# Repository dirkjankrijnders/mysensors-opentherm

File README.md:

# mysensors-opentherm
Mysensors opentherm gateway

Effectively a open of http://otgw.tclcode.com, but with external power brick and a MYSX-2.0 connector instead of the RS-232 interface. The PCB is designed to fit in [this](http://www.ebay.com/itm/221899779029) enclosure and connect to https://github.com/dirkjankrijnders/MYS-PMS7003.

3D render of the PCB:

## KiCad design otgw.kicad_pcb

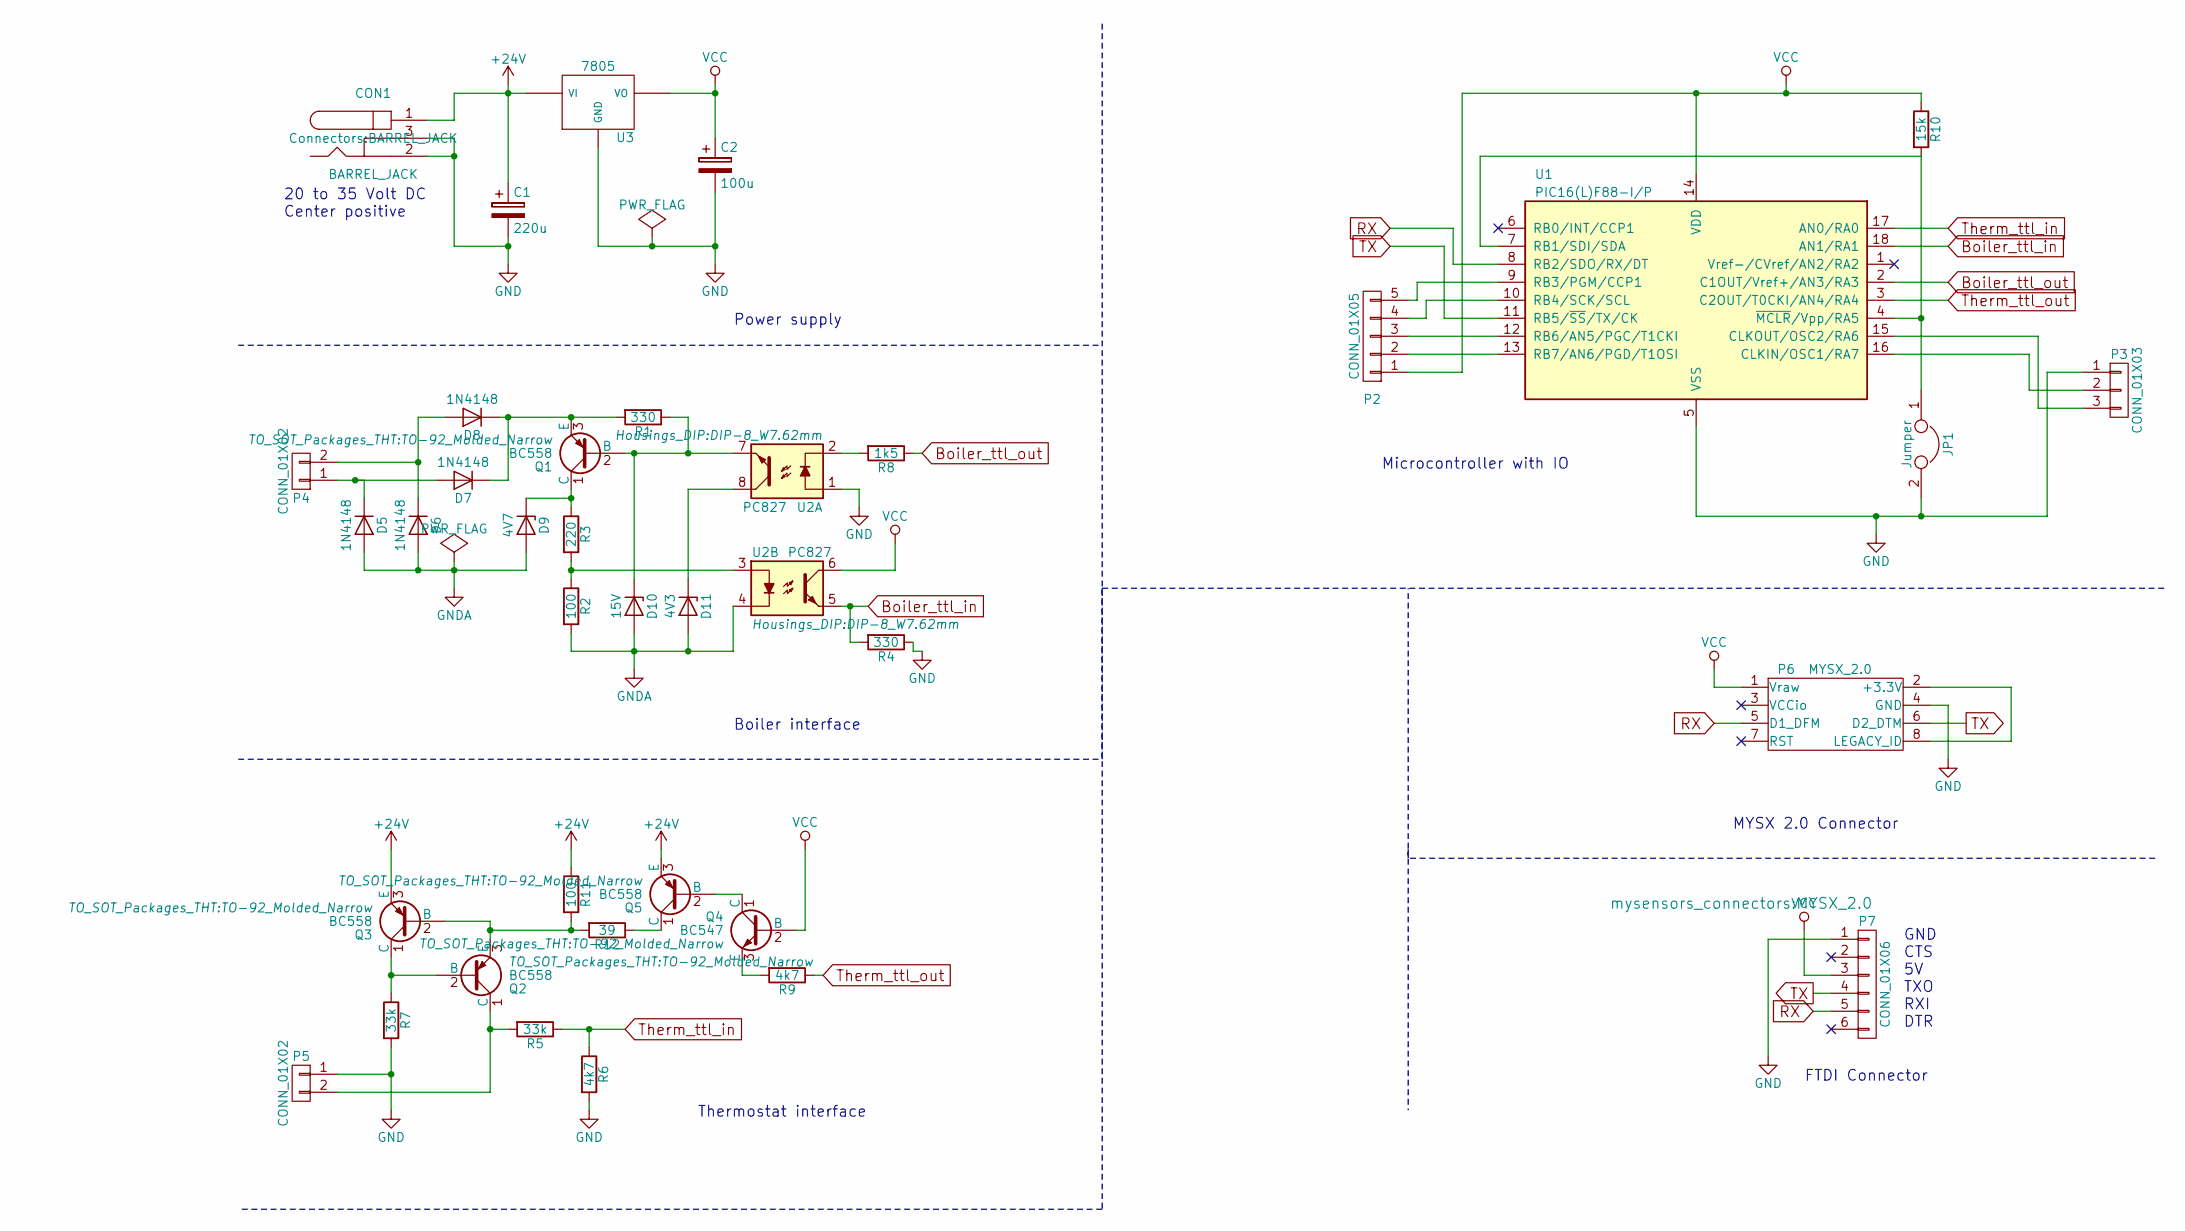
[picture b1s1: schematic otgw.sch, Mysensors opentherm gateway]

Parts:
C1: 220u; CP_Radial_D10.0mm_P5.00mm_P7.50mm
C2: 100u; CP_Radial_D10.0mm_P5.00mm_P7.50mm
CON1: BARREL_JACK
D5, D6, D7, D8: 1N4148; D_DO-35_SOD27_P7.62mm_Horizontal
D9: 4V7; D_DO-35_SOD27_P7.62mm_Horizontal
D10: 15V; D_DO-35_SOD27_P7.62mm_Horizontal
D11: 4V3; D_DO-35_SOD27_P7.62mm_Horizontal
JP1: Jumper; Pin_Header_Angled_1x02_Pitch2.54mm
P2: CONN_01X05; Pin_Header_Straight_1x05_Pitch2.54mm
P3: CONN_01X03; Pin_Header_Straight_1x03_Pitch2.54mm
P4, P5: CONN_01X02; PhoenixContact_MSTBA-G_02x5.00mm_Angled
P6: MYSX_2.0
P7: CONN_01X06; Pin_Header_Straight_1x06_Pitch2.54mm
Q1, Q2, Q3, Q5: BC558; TO-92_Molded_Narrow
Q4: BC547; TO-92_Molded_Narrow
R1, R4: 330; R_Axial_DIN0207_L6.3mm_D2.5mm_P7.62mm_Horizontal
R2, R11: 100; R_Axial_DIN0207_L6.3mm_D2.5mm_P7.62mm_Horizontal
R3: 220; R_Axial_DIN0207_L6.3mm_D2.5mm_P7.62mm_Horizontal
R5, R7: 33k; R_Axial_DIN0207_L6.3mm_D2.5mm_P7.62mm_Horizontal
R6, R9: 4k7; R_Axial_DIN0207_L6.3mm_D2.5mm_P7.62mm_Horizontal
R8: 1k5; R_Axial_DIN0207_L6.3mm_D2.5mm_P7.62mm_Horizontal
R10: 15k; R_Axial_DIN0207_L6.3mm_D2.5mm_P7.62mm_Horizontal
R12: 39; R_Axial_DIN0207_L6.3mm_D2.5mm_P7.62mm_Horizontal
U1: PIC16(L)F88-I/P; DIP-18_W7.62mm
U2: PC827; DIP-8_W7.62mm
U3: 7805; TO-220_Vertical

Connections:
+24V: C1.1, CON1.1, Q3.3 (E), Q5.3 (E), R11.1, U3.1 (VI)
Boiler_ttl_in: R4.2, U1.18 (AN1/RA1), U2.5
Boiler_ttl_out: R8.1, U1.2 (C1OUT/Vref+/AN3/RA3)
GND: C1.2, C2.2, CON1.2, CON1.3, JP1.2, P3.1, P5.1, P6.4 (GND), P7.1, R4.1, R6.2, R7.2, U1.5 (VSS), U2.1, U3.2 (GND)
GNDA: D5.2 (A), D6.2 (A), D9.2 (A), D10.2 (A), D11.2 (A), R2.2, U2.4
unnamed: D5.1 (K), D7.2 (A), P4.1
unnamed: D6.1 (K), D8.2 (A), P4.2
unnamed: D7.1 (K), D8.1 (K), Q1.3 (E), R1.2
unnamed: D9.1 (K), Q1.1 (C), R3.1
unnamed: D10.1 (K), Q1.2 (B), R1.1, U2.7
unnamed: D11.1 (K), U2.8
unnamed: JP1.1, R10.2, U1.4 (~MCLR~/Vpp/RA5), U1.7 (RB1/SDI/SDA)
unnamed: P2.2, U1.13 (RB7/AN6/PGD/T1OSI)
unnamed: P2.3, U1.12 (RB6/AN5/PGC/T1CKI)
unnamed: P2.4, U1.10 (RB4/SCK/SCL)
unnamed: P2.5, U1.9 (RB3/PGM/CCP1)
unnamed: P3.2, U1.16 (CLKIN/OSC1/RA7)
unnamed: P3.3, U1.15 (CLKOUT/OSC2/RA6)
unnamed: P5.2, Q2.1 (C), R5.2
unnamed: P6.2 (+3.3V), P6.8 (LEGACY_ID)
unnamed: Q2.2 (B), Q3.1 (C), R7.1
unnamed: Q2.3 (E), Q3.2 (B), R11.2, R12.2
unnamed: Q4.1 (C), Q5.2 (B)
unnamed: Q4.3 (E), R9.2
unnamed: Q5.1 (C), R12.1
unnamed: R2.1, R3.2, U2.3
unnamed: R8.2, U2.2
RX: P6.5 (D1_DFM), P7.5, U1.8 (RB2/SDO/RX/DT)
TX: P6.6 (D2_DTM), P7.4, U1.11 (RB5/~SS~/TX/CK)
Therm_ttl_in: R5.1, R6.1, U1.17 (AN0/RA0)
Therm_ttl_out: R9.1, U1.3 (C2OUT/T0CKI/AN4/RA4)
VCC: C2.1, P2.1, P6.1 (Vraw), P7.3, Q4.2 (B), R10.1, U1.14 (VDD), U2.6, U3.3 (VO)

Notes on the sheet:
GND CTS 5V TXO RXI DTR
MYSX 2.0 Connector
FTDI Connector
Thermostat interface
Boiler interface
Power supply
20 to 35 Volt DC Center positive
Microcontroller with IO

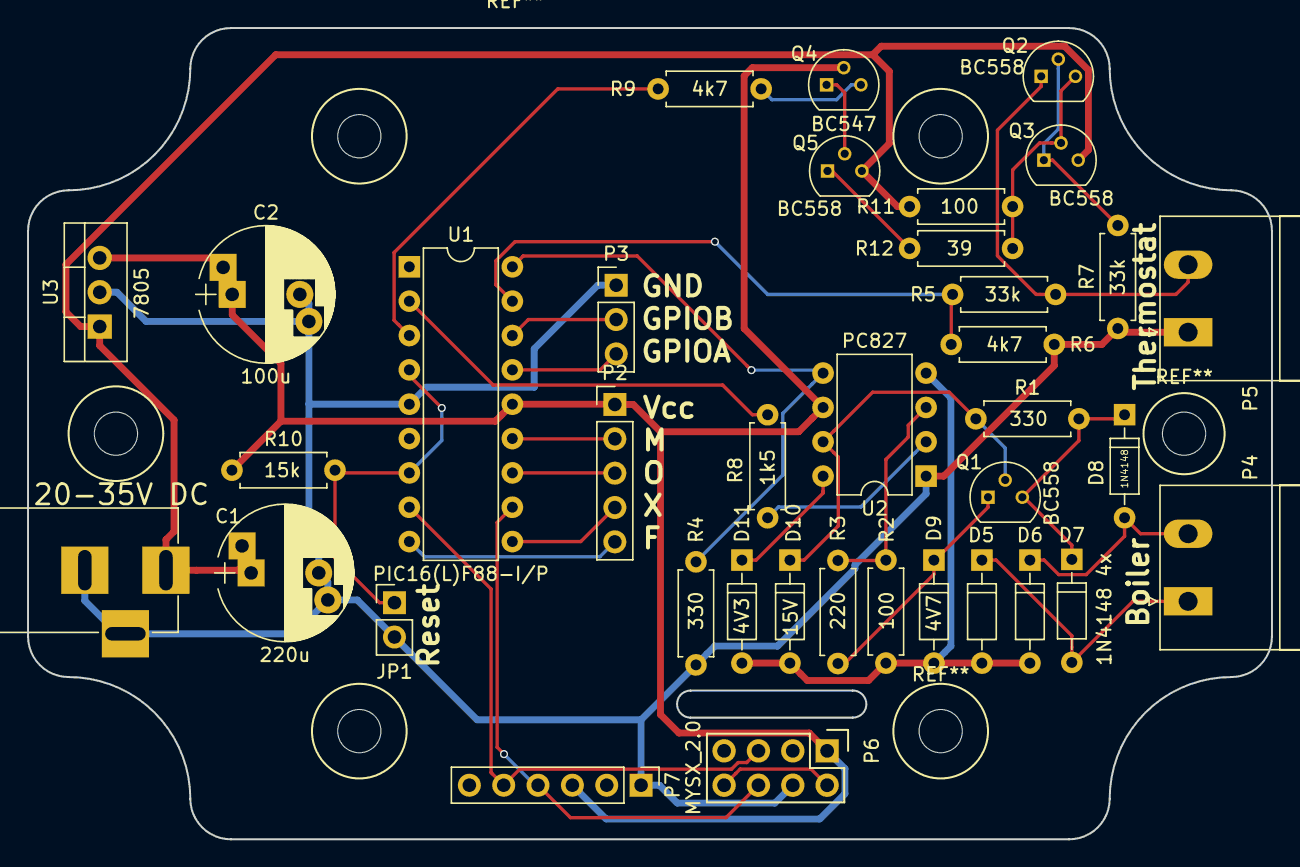
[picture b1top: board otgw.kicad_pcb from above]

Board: 2 copper layers, 92.0 x 60.0 mm, 37 parts (0 on the bottom side), 32 nets.

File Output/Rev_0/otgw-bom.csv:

Reference, Value, Footprint, Datasheet
"P4","CONN_01X02","Connectors_Phoenix:PhoenixContact_MSTBA-G_02x5.00mm_Angled",""
"P5","CONN_01X02","Connectors_Phoenix:PhoenixContact_MSTBA-G_02x5.00mm_Angled",""
"C1","220u","Capacitors_THT:CP_Radial_D10.0mm_P5.00mm_P7.50mm",""
"U3","7805","TO_SOT_Packages_THT:TO-220_Vertical",""
"C2","100u","Capacitors_THT:CP_Radial_D10.0mm_P5.00mm_P7.50mm",""
"U1","PIC16(L)F88-I/P","Housings_DIP:DIP-18_W7.62mm",""
"R10","15k","Resistors_THT:R_Axial_DIN0207_L6.3mm_D2.5mm_P7.62mm_Horizontal",""
"JP1","Jumper","Pin_Headers:Pin_Header_Angled_1x02_Pitch2.54mm",""
"P3","CONN_01X03","Pin_Headers:Pin_Header_Straight_1x03_Pitch2.54mm",""
"P2","CONN_01X05","Pin_Headers:Pin_Header_Straight_1x05_Pitch2.54mm",""
"D5","1N4148","Diodes_THT:D_DO-35_SOD27_P7.62mm_Horizontal",""
"D6","1N4148","Diodes_THT:D_DO-35_SOD27_P7.62mm_Horizontal",""
"D7","1N4148","Diodes_THT:D_DO-35_SOD27_P7.62mm_Horizontal",""
"D8","1N4148","Diodes_THT:D_DO-35_SOD27_P7.62mm_Horizontal",""
"D9","4V7","Diodes_THT:D_DO-35_SOD27_P7.62mm_Horizontal",""
"Q1","BC558","TO_SOT_Packages_THT:TO-92_Molded_Narrow",""
"R1","330","Resistors_THT:R_Axial_DIN0207_L6.3mm_D2.5mm_P7.62mm_Horizontal",""
"R3","220","Resistors_THT:R_Axial_DIN0207_L6.3mm_D2.5mm_P7.62mm_Horizontal",""
"R2","100","Resistors_THT:R_Axial_DIN0207_L6.3mm_D2.5mm_P7.62mm_Horizontal",""
"D10","15V","Diodes_THT:D_DO-35_SOD27_P7.62mm_Horizontal",""
"D11","4V3","Diodes_THT:D_DO-35_SOD27_P7.62mm_Horizontal",""
"U2","PC827","Housings_DIP:DIP-8_W7.62mm",""
"R8","1k5","Resistors_THT:R_Axial_DIN0207_L6.3mm_D2.5mm_P7.62mm_Horizontal",""
"R4","330","Resistors_THT:R_Axial_DIN0207_L6.3mm_D2.5mm_P7.62mm_Horizontal",""
"Q3","BC558","TO_SOT_Packages_THT:TO-92_Molded_Narrow",""
"Q2","BC558","TO_SOT_Packages_THT:TO-92_Molded_Narrow",""
"R7","33k","Resistors_THT:R_Axial_DIN0207_L6.3mm_D2.5mm_P7.62mm_Horizontal",""
"R5","33k","Resistors_THT:R_Axial_DIN0207_L6.3mm_D2.5mm_P7.62mm_Horizontal",""
"R6","4k7","Resistors_THT:R_Axial_DIN0207_L6.3mm_D2.5mm_P7.62mm_Horizontal",""
"R11","100","Resistors_THT:R_Axial_DIN0207_L6.3mm_D2.5mm_P7.62mm_Horizontal",""
"R12","39","Resistors_THT:R_Axial_DIN0207_L6.3mm_D2.5mm_P7.62mm_Horizontal",""
"Q5","BC558","TO_SOT_Packages_THT:TO-92_Molded_Narrow",""
"Q4","BC547","TO_SOT_Packages_THT:TO-92_Molded_Narrow",""
"R9","4k7","Resistors_THT:R_Axial_DIN0207_L6.3mm_D2.5mm_P7.62mm_Horizontal",""
"P7","CONN_01X06","Pin_Headers:Pin_Header_Straight_1x06_Pitch2.54mm",""
"P6","MYSX_2.0","mysensors_connectors:MYSX_2.0",""
"CON1","BARREL_JACK","Connectors:BARREL_JACK",""

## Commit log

2017-06-16 Added PCB design files
2017-06-16 Added standard BOM from KiCad
2017-06-16 Added a slot for the MYSX cable to go to the other side of the board
2017-06-16 Adjusted GND plane to recent changes
2017-06-19 Added production outputs
2017-06-19 Fixed the silk screen
2017-06-19 Annotations on the schematic and some small Silkscreen additions
2017-06-19 Centered a mounting hole
2017-06-19 Added 3D render
2017-06-19 Better image
